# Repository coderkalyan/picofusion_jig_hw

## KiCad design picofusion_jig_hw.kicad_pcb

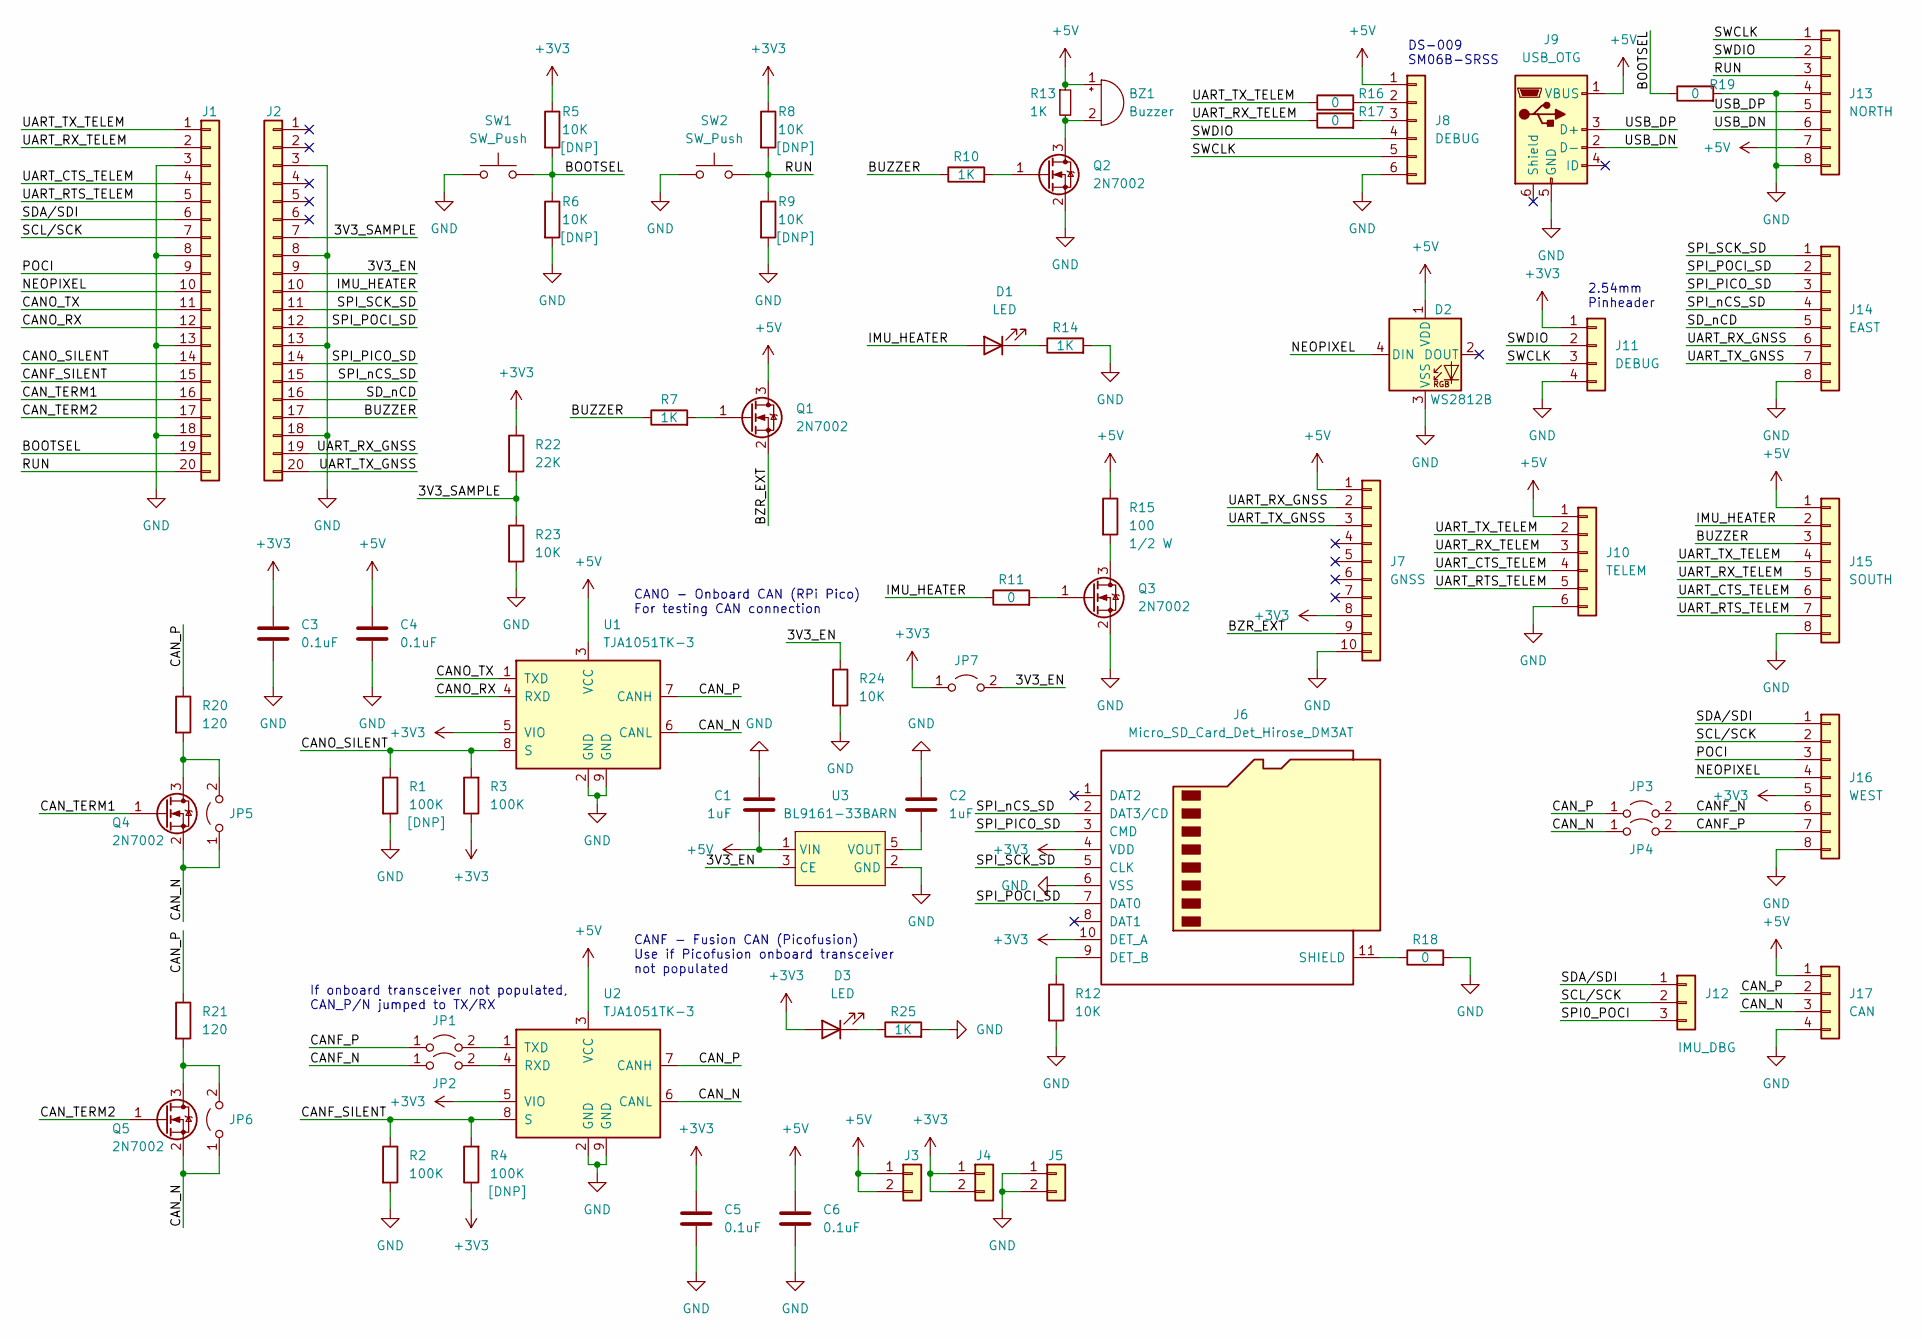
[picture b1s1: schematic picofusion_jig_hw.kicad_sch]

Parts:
BZ1: Buzzer; Buzzer_Murata_PKMCS0909E
C1, C2: 1uF; C_0603_1608Metric
C3, C4, C5, C6: 0.1uF; C_0603_1608Metric; LCSC C1525
D1, D3: LED; LED_0603_1608Metric
D2: WS2812B; LED_WS2812B_PLCC4_5.0x5.0mm_P3.2mm
J1: PICO_WEST; PinSocket_1x20_P2.54mm_Vertical_SMD_Pin1Left
J2: PICO_EAST; PinSocket_1x20_P2.54mm_Vertical_SMD_Pin1Left
J3, J4, J5: Conn_01x02; PinHeader_1x02_P2.54mm_Vertical
J6: Micro_SD_Card_Det_Hirose_DM3AT; microSD_HC_Hirose_DM3AT-SF-PEJM5
J7: GNSS; JST_GH_SM10B-GHS-TB_1x10-1MP_P1.25mm_Horizontal
J8: DEBUG; JST_SH_SM06B-SRSS-TB_1x06-1MP_P1.00mm_Horizontal
J9: USB_OTG; XKB_U254-051T-4BH83-F1S
J10: TELEM; JST_GH_SM06B-GHS-TB_1x06-1MP_P1.25mm_Horizontal
J11: DEBUG; PinHeader_1x04_P2.54mm_Vertical
J12: IMU_DBG; PinHeader_1x03_P2.54mm_Vertical
J13: NORTH; Castellated_1x8_P2.54mm_Vertical
J14: EAST; Castellated_1x8_P2.54mm_Vertical
J15: SOUTH; Castellated_1x8_P2.54mm_Vertical
J16: WEST; Castellated_1x8_P2.54mm_Vertical
J17: CAN; JST_GH_SM04B-GHS-TB_1x04-1MP_P1.25mm_Horizontal
JP1, JP2, JP3, JP4, JP5, JP6, JP7: Jumper_2_Open; PinHeader_1x02_P2.54mm_Vertical
Q1, Q2, Q3, Q4, Q5: 2N7002; SOT-23
R1, R2, R3, R4: 100K; R_0603_1608Metric; LCSC C25741
R5, R6, R8, R9, R12, R23, R24: 10K; R_0603_1608Metric
R7, R10, R13, R14, R25: 1K; R_0603_1608Metric
R11, R16, R17, R18, R19: 0; R_0603_1608Metric
R15: 100; R_0603_1608Metric
R20, R21: 120; R_0603_1608Metric
R22: 22K; R_0603_1608Metric
SW1, SW2: SW_Push; PTS815 SJM 250 SMTR LFS
U1, U2: TJA1051TK-3; DFN-8-1EP_3x3mm_P0.65mm_EP1.55x2.4mm; LCSC C124020
U3: BL9161-33BARN; SOT-23-5

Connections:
+3V3: C3.1, C5.1, D3.2 (A), J4.1, J4.2, J6.4 (VDD), J6.10 (DET_A), J7.8, J11.1, J16.5, JP7.1 (A), R3.1, R4.1, R5.1, R8.1, R22.1, U1.5 (VIO), U2.5 (VIO)
+5V: BZ1.1 (-), C1.2, C4.1, C6.1, D2.1 (VDD), J3.1, J3.2, J7.1, J8.1, J9.1 (VBUS), J10.1, J13.7, J15.1, J17.1, Q1.3 (D), R13.1, R15.1, U1.3 (VCC), U2.3 (VCC), U3.1 (VIN)
/3V3_EN: J2.9, JP7.2 (B), R24.1, U3.3 (CE)
/3V3_SAMPLE: J2.7, R22.2, R23.1
/BOOTSEL: J1.19, R5.2, R6.1, R19.1, SW1.2
/BUZZER: J2.17, J15.3, R7.1, R10.1
/BZR_EXT: J7.9, Q1.2 (S)
/CANF_N: J16.6, JP2.1 (A), JP3.2 (B)
/CANF_P: J16.7, JP1.1 (A), JP4.2 (B)
/CANF_SILENT: J1.15, R2.1, R4.2, U2.8 (S)
/CANO_RX: J1.12, U1.4 (RXD)
/CANO_SILENT: J1.14, R1.1, R3.2, U1.8 (S)
/CANO_TX: J1.11, U1.1 (TXD)
/CAN_N: J17.3, JP4.1 (A), JP5.1 (A), JP6.1 (A), Q4.2 (S), Q5.2 (S), U1.6 (CANL), U2.6 (CANL)
/CAN_P: J17.2, JP3.1 (A), R20.1, R21.1, U1.7 (CANH), U2.7 (CANH)
/CAN_TERM1: J1.16, Q4.1 (G)
/CAN_TERM2: J1.17, Q5.1 (G)
/IMU_HEATER: D1.2 (A), J2.10, J15.2, R11.1
/NEOPIXEL: D2.4 (DIN), J1.10, J16.4
/POCI: J1.9, J16.3
/RUN: J1.20, J13.3, R8.2, R9.1, SW2.2
/SCL/SCK: J1.7, J12.2, J16.2
/SDA/SDI: J1.6, J12.1, J16.1
/SD_nCD: J2.16, J14.5
/SPI0_POCI: J12.3
/SPI_PICO_SD: J2.14, J6.3 (CMD), J14.3
/SPI_POCI_SD: J2.12, J6.7 (DAT0), J14.2
/SPI_SCK_SD: J2.11, J6.5 (CLK), J14.1
/SPI_nCS_SD: J2.15, J6.2 (DAT3/CD), J14.4
/SWCLK: J8.5, J11.3, J13.1
/SWDIO: J8.4, J11.2, J13.2
/UART_CTS_TELEM: J1.4, J10.4, J15.6
/UART_RTS_TELEM: J1.5, J10.5, J15.7
/UART_RX_GNSS: J2.19, J7.2, J14.6
/UART_RX_TELEM: J1.2, J10.3, J15.5, R17.1
/UART_TX_GNSS: J2.20, J7.3, J14.7
/UART_TX_TELEM: J1.1, J10.2, J15.4, R16.1
/USB_DN: J9.2 (D-), J13.6
/USB_DP: J9.3 (D+), J13.5
GND: C1.1, C2.1, C3.2, C4.2, C5.2, C6.2, D2.3 (VSS), J1.3, J1.8, J1.13, J1.18, J2.3, J2.8, J2.13, J2.18, J5.1, J5.2, J6.6 (VSS), J7.10, J8.6, J9.5 (GND), J10.6, J11.4, J13.4, J13.8, J14.8, J15.8, J16.8, J17.4, Q2.2 (S), Q3.2 (S), R1.2, R2.2, R6.2, R9.2, R12.2, R14.2, R18.2, R19.2, R23.2, R24.2, R25.2, SW1.1, SW2.1, U1.2 (GND), U1.9 (GND), U2.2 (GND), U2.9 (GND), U3.2 (GND)
unnamed: BZ1.2 (+), Q2.3 (D), R13.2
unnamed: C2.2, U3.5 (VOUT)
unnamed: D1.1 (K), R14.1
unnamed: D3.1 (K), R25.1
unnamed: J6.9 (DET_B), R12.1
unnamed: J6.11 (SHIELD), R18.1
unnamed: J8.2, R16.2
unnamed: J8.3, R17.2
unnamed: JP1.2 (B), U2.1 (TXD)
unnamed: JP2.2 (B), U2.4 (RXD)
unnamed: JP5.2 (B), Q4.3 (D), R20.2
unnamed: JP6.2 (B), Q5.3 (D), R21.2
unnamed: Q1.1 (G), R7.2
unnamed: Q2.1 (G), R10.2
unnamed: Q3.1 (G), R11.2
unnamed: Q3.3 (D), R15.2

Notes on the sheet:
CANO - Onboard CAN (RPi Pico) For testing CAN connection
If onboard transceiver not populated, CAN_P/N jumped to TX/RX
DS-009 SM06B-SRSS
CANF - Fusion CAN (Picofusion) Use if Picofusion onboard transceiver not populated
2.54mm Pinheader

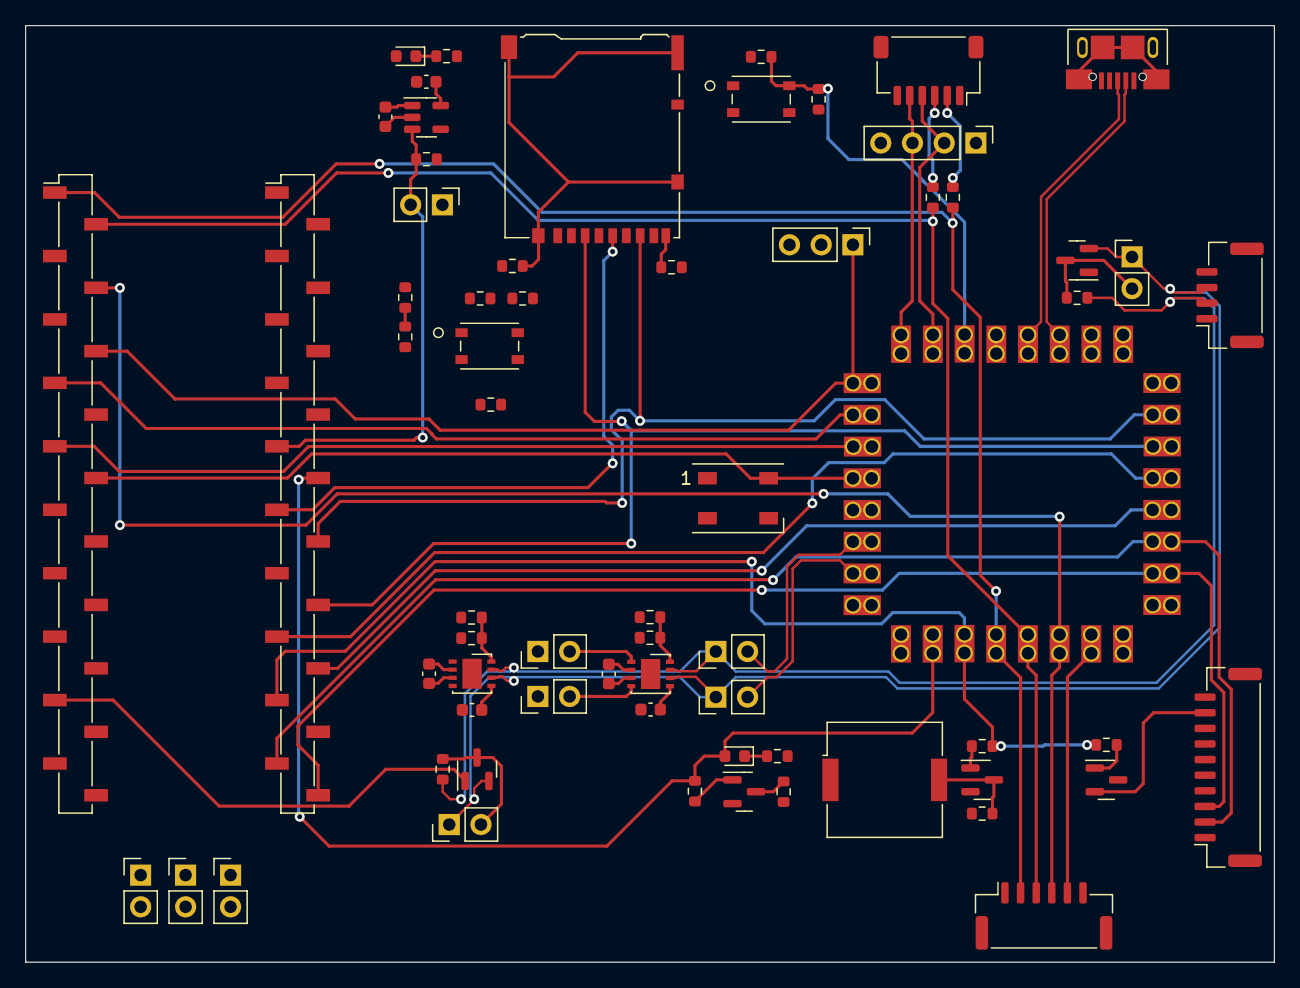
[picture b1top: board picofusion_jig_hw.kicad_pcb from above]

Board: 2 copper layers, 100.0 x 75.0 mm, 69 parts (0 on the bottom side), 55 nets.

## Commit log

2022-09-18 schematic: initial commit
2022-10-16 Layout draft

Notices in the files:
parts and their libraries:
Copyright 2021 Accelerated Designs. All rights reserved.
